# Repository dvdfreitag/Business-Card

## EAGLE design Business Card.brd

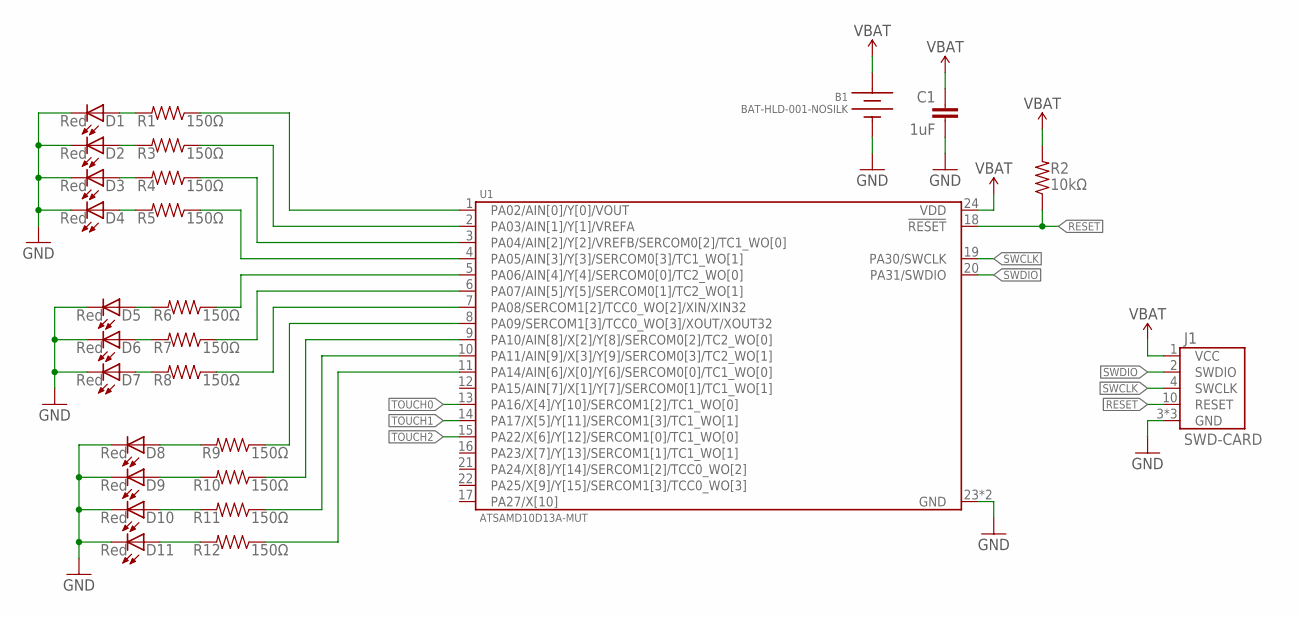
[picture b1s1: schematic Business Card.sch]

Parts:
B1: BAT-HLD-001-NOSILK; BK-912-G-TR
C1: 1uF; 0603-CAP
D1, D2, D3, D4, D5, D6, D7, D8, D9, D10, D11: Red; 0805-LED
J1: SWD-CARD; CWR-170-10-0203
R1, R3, R4, R5, R6, R7, R8, R9, R10, R11, R12: 150Ω; 0603-CAP
R2: 10kΩ; 0603-CAP
U1: ATSAMD10D13A-MUT; QFN-24

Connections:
GND: B1.- (N), C1.2, D1.C, D2.C, D3.C, D4.C, D5.C, D6.C, D7.C, D8.C, D9.C, D10.C, D11.C, J1.3 (GND), J1.5 (GND), J1.9 (GND), U1.23 (GND), U1.P$1 (GND)
unnamed: D1.A, R1.2
unnamed: D5.A, R6.2
unnamed: D2.A, R3.2
unnamed: D6.A, R7.2
unnamed: D3.A, R4.2
unnamed: D7.A, R8.2
unnamed: D4.A, R5.2
unnamed: D8.A, R9.2
unnamed: D9.A, R10.2
unnamed: D10.A, R11.2
unnamed: D11.A, R12.2
unnamed: R5.1, U1.4 (PA05/AIN[3]/Y[3]/SERCOM0[3]/TC1_WO[1])
unnamed: R4.1, U1.3 (PA04/AIN[2]/Y[2]/VREFB/SERCOM0[2]/TC1_W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)
unnamed: R3.1, U1.2 (PA03/AIN[1]/Y[1]/VREFA)
unnamed: R1.1, U1.1 (PA02/AIN[0]/Y[0]/VOUT)
unnamed: R6.1, U1.5 (PA06/AIN[4]/Y[4]/SERCOM0[0]/TC2_WO[0])
unnamed: R7.1, U1.6 (PA07/AIN[5]/Y[5]/SERCOM0[1]/TC2_WO[1])
unnamed: R8.1, U1.7 (PA08/SERCOM1[2]/TCC0_WO[2]/XIN/XIN32)
unnamed: R9.1, U1.8 (PA09/SERCOM1[3]/TCC0_WO[3]/XOUT/XOUT32)
unnamed: R10.1, U1.9 (PA10/AIN[8]/X[2]/Y[8]/SERCOM0[2]/TC2_WO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)
unnamed: R11.1, U1.10 (PA11/AIN[9]/X[3]/Y[9]/SERCOM0[3]/TC2_WO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)
unnamed: R12.1, U1.11 (PA14/AIN[6]/X[0]/Y[6]/SERCOM0[0]/TC1_WO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)
RESET: J1.10 (RESET), R2.1, U1.18 (!RESET)
SWCLK: J1.4 (SWCLK), U1.19 (PA30/SWCLK)
SWDIO: J1.2 (SWDIO), U1.20 (PA31/SWDIO)
TOUCH0: U1.13 (PA16/X[4]/Y[10]/SERCOM1[2]/TC1_WO[0])
TOUCH1: U1.14 (PA17/X[5]/Y[11]/SERCOM1[3]/TC1_WO[1])
TOUCH2: U1.15 (PA22/X[6]/Y[12]/SERCOM1[0]/TC1_WO[0])
VBAT: B1.+1, B1.+2, C1.1, J1.1 (VCC), R2.2, U1.24 (VDD)

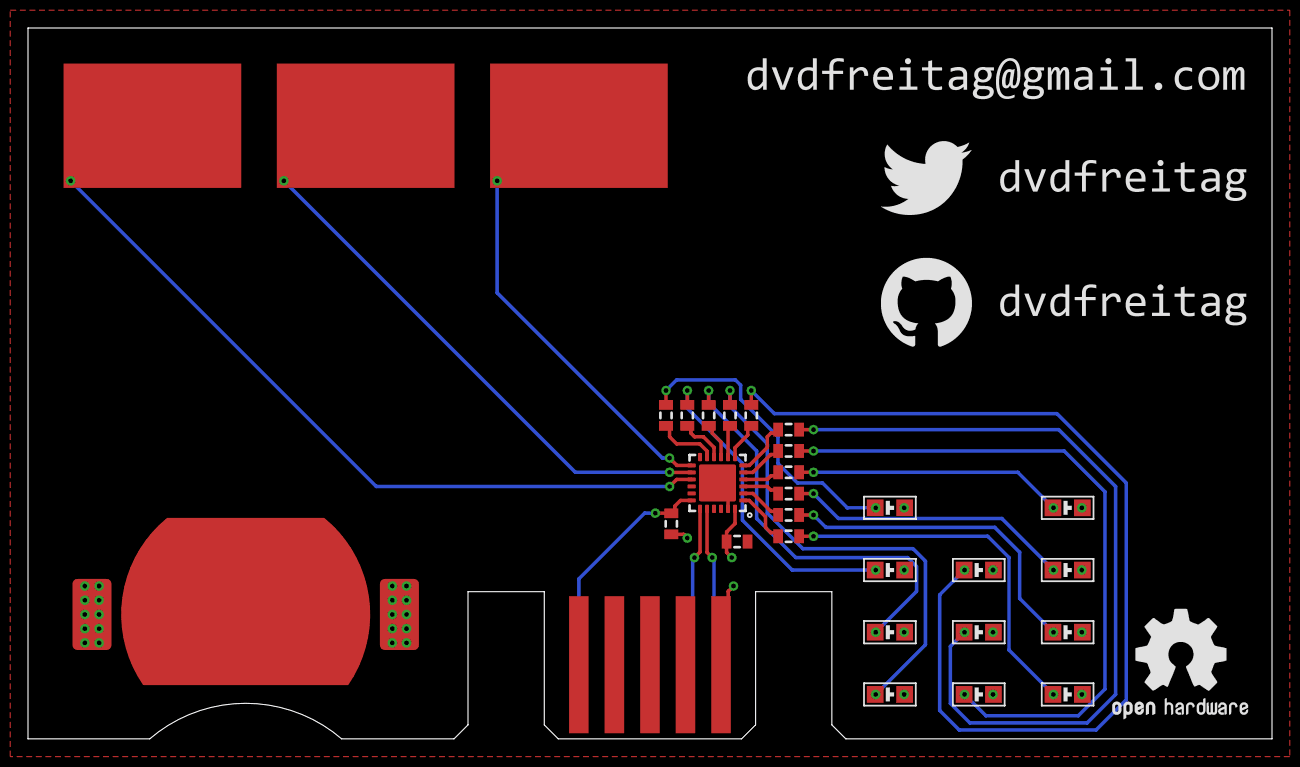
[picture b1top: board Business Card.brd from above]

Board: 2 copper layers, 88.9 x 50.8 mm, 31 parts (0 on the bottom side), 27 nets.

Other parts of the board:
U$1: GITHUB
U$2: TWITTER
U$3: OSHW
U$4: EMAIL

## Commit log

2016-08-11 Create LICENSE
